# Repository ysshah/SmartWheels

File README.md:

# SmartWheels

## Set up the Raspberry Pi

1. Download Raspbian Jessie from [here](https://www.raspberrypi.org/downloads/raspbian/).
2. Mount the image onto an SD card using these [instructions](https://www.raspberrypi.org/documentation/installation/installing-images/).
3. Follow the on-screen instructions to set up Raspberry Pi.
4. Run `sudo raspi-config` and set locale, timezone, keyboard (GB => US).
5. Update packages with `sudo apt-get update` followed by `sudo apt-get upgrade`.
6. Install git with `sudo apt-get install git`.

## R-NET Setup

Clone Stephen Chavez's repository
```
git clone https://github.com/redragonx/can2RNET
```

Install can-utils
```
sudo apt-get install can-utils
```

Add the following lines to /boot/config.txt
```
dtparam=spi=on
dtoverlay=mcp2515-can0,oscillator=16000000,interrupt=25
dtoverlay=spi-bcm2835
```

Add the following lines to /etc/network/interfaces
```
allow-hotplug can0
iface can0 can static
    bitrate 125000
    up /sbin/ip link set $IFACE down
    up /sbin/ip link set $IFACE up
```

Add these kernel modules to /etc/modules
```
mcp251x
can_dev
```

Boot with everything connected and run
```
python3 JoyLocal.py
```

## SSH to Raspberry Pi

1. Connect the computer to a WiFi network. Since CalVisitor doesn't support local SSH and AirBears2 is difficult to set up on the Raspberry Pi, we use enable a Personal Hotspot on an iPhone (Settings > Personal Hotspot) to use as our local WiFi network.
2. Connect Raspberry Pi to the same WiFi network using these [instructions](https://www.raspberrypi.org/documentation/configuration/wireless/wireless-cli.md).
3. SSH using these [instructions](https://www.raspberrypi.org/documentation/remote-access/ssh/unix.md).
4. (Optional) Set up a permanent IP address for the Raspberry Pi using either this [link](https://www.modmypi.com/blog/how-to-give-your-raspberry-pi-a-static-ip-address-update) or the second comment in this [link](https://www.modmypi.com/blog/tutorial-how-to-give-your-raspberry-pi-a-static-ip-address). Not sure which one did the trick.
5. (Optional) Enable password-less SSH by copying the contents of the computer's id_rsa.pub file to the Raspberry Pi's ~/.ssh/authorized_keys file.

## AprilTags on iPhone to Raspberry Pi

1. Download the [AprilTag application](https://itunes.apple.com/us/app/apriltag/id736108128) on the iPhone.
2. Tap the yellow text on the top left corner to go to settings, enter the Raspberry Pi's IP address into the "UDP Transmit Addr" field, and turn on the "UDP Transmit Enabled" switch.
3. Receive the UDP packets on port 7709 according to the [AprilTags wiki](https://april.eecs.umich.edu/wiki/AprilTags). See their example decoder written in Java [here](https://april.eecs.umich.edu/apriltag/AprilTagReceive.java).

## Discontinued Instructions

### AprilTags on Raspberry Pi

#### RaspiCam

Install OpenCV so that RaspiCam compiles with OpenCV compatibility
```
sudo apt-get install libopencv-dev
```

Clone repository (fixes BGR issues from original [SVN repository](https://sourceforge.net/projects/raspicam/files/))
```
git clone https://github.com/6by9/raspicam-0.1.3
```

Following these [instructions](https://www.uco.es/investiga/grupos/ava/node/40)...
```
cd raspicamxx
mkdir build
cd build
cmake ..
```

Verify that `-- CREATE OPENCV MODULE=1` in the output, then run
```
make
sudo make install
sudo ldconfig
```

#### AprilTags

Following these [instructions](http://people.csail.mit.edu/kaess/apriltags/)...

Install dependencies
```
sudo apt-get install subversion cmake libopencv-dev libeigen3-dev libv4l-dev
```

Clone repository
```
git clone https://github.com/ysshah/SmartWheels.git
```

Compile and run
```
cd SmartWheels
make
./build/bin/apriltags_demo
```

### Installing OpenCV and Python

Follow [this OpenCV guide](http://www.pyimagesearch.com/2016/04/18/install-guide-raspberry-pi-3-raspbian-jessie-opencv-3/) and then [this Python with camera guide](http://www.pyimagesearch.com/2015/03/30/accessing-the-raspberry-pi-camera-with-opencv-and-python/).

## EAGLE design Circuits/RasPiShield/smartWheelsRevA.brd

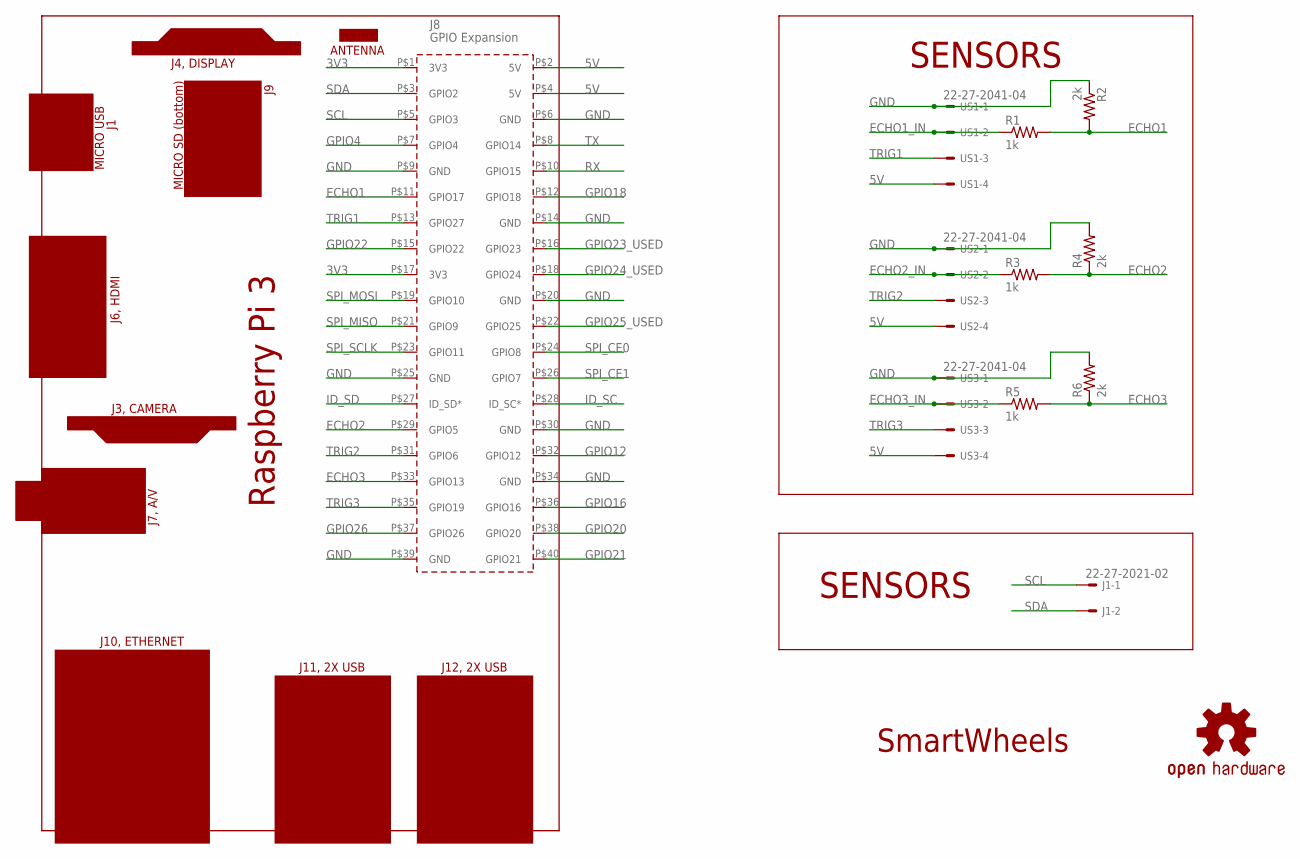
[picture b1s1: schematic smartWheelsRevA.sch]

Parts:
J1: 22-27-2021-02; 6410-02
LOGO1: OSHW-LOGOL-TOP; OSHW_LOGO_L_TOP
PCB2: RPI3
R1, R3, R5: 1k; M0805
R2, R4, R6: 2k; M0805
US1, US2, US3: 22-27-2041-04; 6410-04

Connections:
3V3: PCB2.P$1 (3V3), PCB2.P$17 (3V3)
5V: PCB2.P$2 (5V), PCB2.P$4 (5V), US1.4, US2.4, US3.4
ECHO1: PCB2.P$11 (GPIO17), R1.2, R2.2
ECHO1_IN: R1.1, US1.2
ECHO2: PCB2.P$29 (GPIO5), R3.2, R4.1
ECHO2_IN: R3.1, US2.2
ECHO3: PCB2.P$33 (GPIO13), R5.2, R6.1
ECHO3_IN: R5.1, US3.2
GND: PCB2.P$6 (GND), PCB2.P$9 (GND), PCB2.P$14 (GND), PCB2.P$20 (GND), PCB2.P$25 (GND), PCB2.P$30 (GND), PCB2.P$34 (GND), PCB2.P$39 (GND), R2.1, R4.2, R6.2, US1.1, US2.1, US3.1
GPIO4: PCB2.P$7 (GPIO4)
GPIO12: PCB2.P$32 (GPIO12)
GPIO16: PCB2.P$36 (GPIO16)
GPIO18: PCB2.P$12 (GPIO18)
GPIO20: PCB2.P$38 (GPIO20)
GPIO21: PCB2.P$40 (GPIO21)
GPIO22: PCB2.P$15 (GPIO22)
GPIO23_USED: PCB2.P$16 (GPIO23)
GPIO24_USED: PCB2.P$18 (GPIO24)
GPIO25_USED: PCB2.P$22 (GPIO25)
GPIO26: PCB2.P$37 (GPIO26)
ID_SC: PCB2.P$28 (ID_SC*)
ID_SD: PCB2.P$27 (ID_SD*)
RX: PCB2.P$10 (GPIO15)
SCL: J1.1, PCB2.P$5 (GPIO3)
SDA: J1.2, PCB2.P$3 (GPIO2)
SPI_CE0: PCB2.P$24 (GPIO8)
SPI_CE1: PCB2.P$26 (GPIO7)
SPI_MISO: PCB2.P$21 (GPIO9)
SPI_MOSI: PCB2.P$19 (GPIO10)
SPI_SCLK: PCB2.P$23 (GPIO11)
TRIG1: PCB2.P$13 (GPIO27), US1.3
TRIG2: PCB2.P$31 (GPIO6), US2.3
TRIG3: PCB2.P$35 (GPIO19), US3.3
TX: PCB2.P$8 (GPIO14)

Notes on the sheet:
SmartWheels
SENSORS

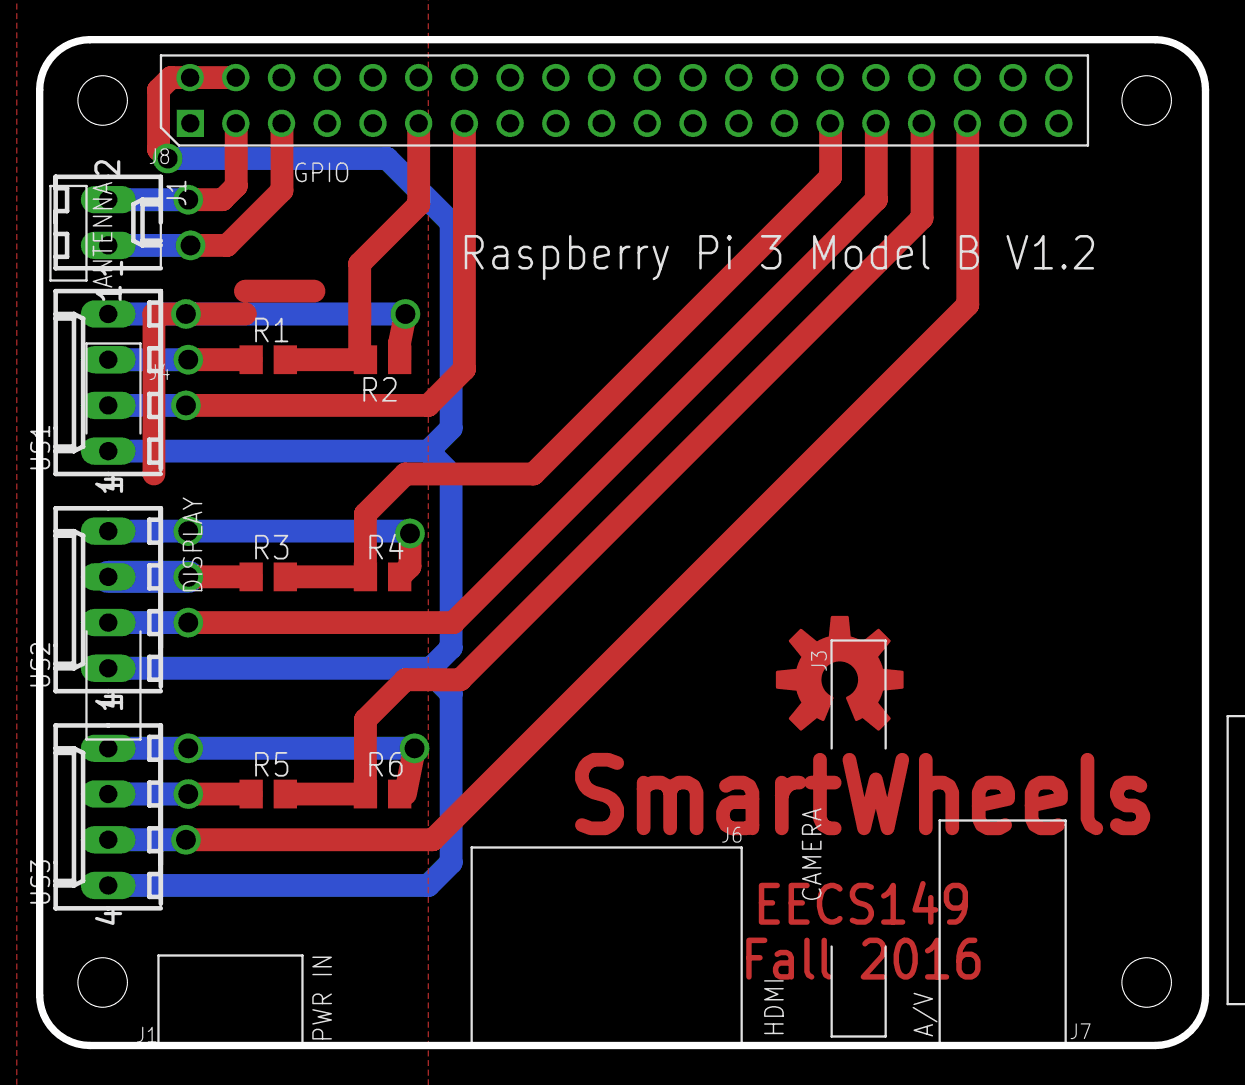
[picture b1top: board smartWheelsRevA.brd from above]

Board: 2 copper layers, 64.8 x 55.9 mm, 12 parts (0 on the bottom side), 14 nets.

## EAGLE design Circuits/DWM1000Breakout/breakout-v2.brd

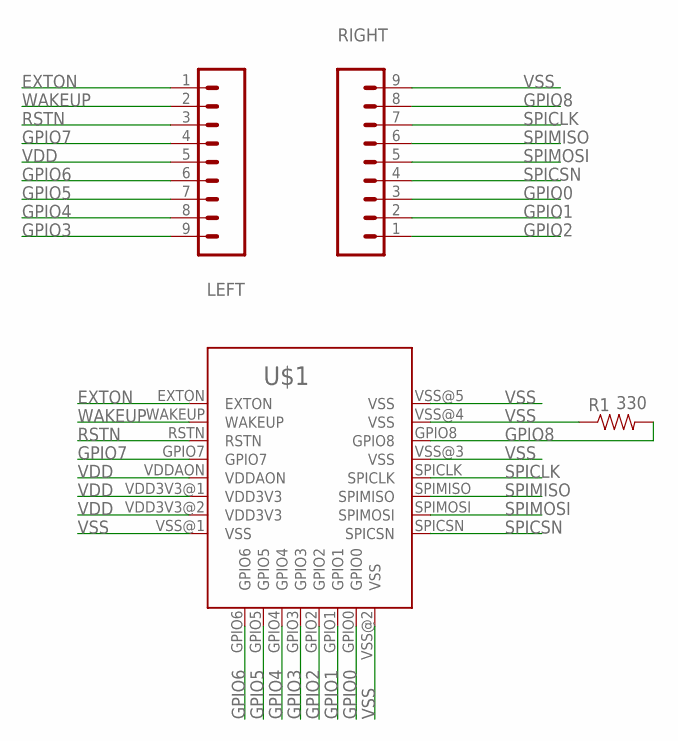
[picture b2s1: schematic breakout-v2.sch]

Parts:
LEFT: M09; 1X09
R1: 330; 0805
RIGHT: M09; 1X09
U$1: DWM1000

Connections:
EXTON: LEFT.1, U$1.EXTON
GPIO0: RIGHT.3, U$1.GPIO0
GPIO1: RIGHT.2, U$1.GPIO1
GPIO2: RIGHT.1, U$1.GPIO2
GPIO3: LEFT.9, U$1.GPIO3
GPIO4: LEFT.8, U$1.GPIO4
GPIO5: LEFT.7, U$1.GPIO5
GPIO6: LEFT.6, U$1.GPIO6
GPIO7: LEFT.4, U$1.GPIO7
GPIO8: R1.2, RIGHT.8, U$1.GPIO8
RSTN: LEFT.3, U$1.RSTN
SPICLK: RIGHT.7, U$1.SPICLK
SPICSN: RIGHT.4, U$1.SPICSN
SPIMISO: RIGHT.6, U$1.SPIMISO
SPIMOSI: RIGHT.5, U$1.SPIMOSI
VDD: LEFT.5, U$1.VDD3V3@1 (VDD3V3), U$1.VDD3V3@2 (VDD3V3), U$1.VDDAON
VSS: R1.1, RIGHT.9, U$1.VSS@1 (VSS), U$1.VSS@2 (VSS), U$1.VSS@3 (VSS), U$1.VSS@4 (VSS), U$1.VSS@5 (VSS)
WAKEUP: LEFT.2, U$1.WAKEUP

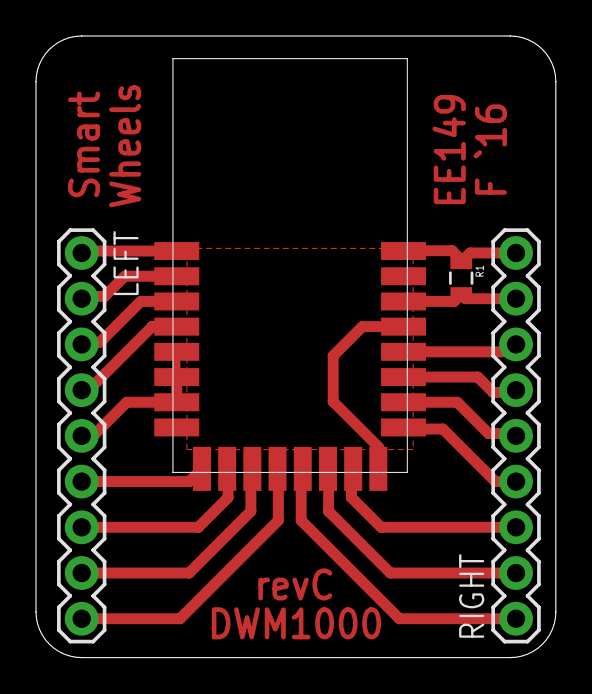
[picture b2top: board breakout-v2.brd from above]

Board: 2 copper layers, 28.9 x 34.5 mm, 4 parts (0 on the bottom side), 18 nets.

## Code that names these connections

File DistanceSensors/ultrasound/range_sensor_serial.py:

import RPi.GPIO as GPIO
import time
GPIO.setmode(GPIO.BCM)

TRIG1 = 22 #output
ECHO1 = 27 #input
TRIG2 = 06 #output
ECHO2 = 13 #input
TRIG3 = 24 #output
ECHO3 = 23 #input
distance1 = 0
distance2 = 0
distance3 = 0


def init_ultra(gpio_in, gpio_out):
    GPIO.setup(gpio_out,GPIO.OUT)
    GPIO.setup(gpio_in,GPIO.IN)

    GPIO.output(gpio_out, False)
    print "Waiting For Sensor To Settle"
    time.sleep(1)

def get_dist(gpio_in, gpio_out, ultrasound):
    global distance1
    global distance2
    global distance3
    GPIO.output(gpio_out, True)
    time.sleep(0.00001)
    GPIO.output(gpio_out, False)
    while GPIO.input(gpio_in)==0:
        pulse_start = time.time()

    while GPIO.input(gpio_in)==1:
        pulse_end = time.time()

    pulse_duration = pulse_end - pulse_start
    distance = pulse_duration * 17150

    distance = round(distance, 2)
    if (ultrasound == 1):
        distance1 = round(distance, 2)
        #print "Distance1: " + str(distance1)
    elif (ultrasound == 2):
        distance2 = round(distance, 2)
        #print "Distance2: " + str(distance2)
    elif (ultrasound == 3):
        distance3 = round(distance, 2)


    #print "Sensor" + str(ultrasound) + "Distance: " +  ":" + str(distance) + " cm",
    time.sleep(0.1)


print "Distance Measurement In Progress"
init_ultra(ECHO1, TRIG1)
init_ultra(ECHO2, TRIG2)
init_ultra(ECHO3, TRIG3)
while True:
    get_dist(ECHO1, TRIG1, 1)
    print "Distance1: " + str(distance1)
    get_dist(ECHO2, TRIG2, 2)
    print "Distance2: " + str(distance2)
    get_dist(ECHO3, TRIG3, 3)
    print "Distance3: " + str(distance3)
    print ""
GPIO.cleanup()

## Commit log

2016-11-13 Initialize AprilTags repo
2016-11-13 Use raspicam for Raspberry Pi camera
2016-11-18 Add .gitignore
2016-12-07 Add raspicam_DIR to CMakeLists
2016-12-10 Move AprilTags to its own folder
2016-12-10 Add README for root folder
2016-12-10 testing raspi shield
2016-12-10 DWM1000
2016-12-10 eagle lib
2016-12-11 Add wheelchair control code
2016-12-11 board ready
2016-12-11 Update README with SSH and iPhone AprilTags instructions
2016-12-12 Add manual override option, rough distance calculation
2016-12-12 Add LIDAR and ultrasound sensor code
2016-12-13 Add packet count as argument for sending custom number of packets
2016-12-13 Add ultrasonic sensor code to smartwheels.py
2016-12-13 utrasound initialization
2016-12-13 trying to merge
2016-12-13 Fix time import issue
2016-12-14 fixed bug: when the april tag is not recognized, the joystick value was not set to 0, continously sending the joystick x and y value of the last position before the tag dissapeared from the camera fi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
2016-12-14 distances threaded
2016-12-15 Change threading to multiprocessing
2016-12-15 Basic obstacle avoidance
2016-12-15 Improve obstacle avoidance and clean code
2016-12-15 Scan for tag if not seen for 3 seconds
2016-12-15 Set scan direction to last seen AprilTag location
2017-04-19 Replace ultrasonic sensors with Lidar
2017-05-02 Add LIDAR obstacle avoidance starter code
2017-05-05 Fix some lines of obstacle avoidance

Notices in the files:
parts and their libraries:
SparkFun-Connectors: Licensing: Creative Commons ShareAlike 4.0 International - https://creativecommons.org/licenses/by-sa/4.0
microbuilder: This work is placed in the public domain, and may be freely used for commercial and non-commercial work with the following conditions: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
